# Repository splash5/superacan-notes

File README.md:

# superacan-notes

All research notes about super acan.

# About the controller

The official super acan controller is hard to find and not good for game playing.
But you can use the SNES controller on super acan with a custom adapter.
The controller protocol is the same as SNES, but the button mapping is a little different.

| Acan | SNES |
|------|------|
|A     |B     |
|B     |Y     |
|START |SELECT|
|SELECT|START |
|Up    |Up    |
|Down  |Down  |
|Left  |Left  |
|Right |Right |
|X     |A     |
|Y     |X     |
|L     |L     |
|R     |R     |

Not very sure and not tested but some game should support multitap (which never officially released, only mentioned on manual).

# About the 6650 chip

This acts as a CIC chip but only contains at least 32 bytes RAM and 16 bytes ROM. (No CPU inside it I guess)
When powering on the 68k CPU runs code which store inside 6619 chip (like Genesis TMSS) and doing some check
about 6650 (like make sure that RAM exists and work properly) and finally reads a special string and compare it.
CPU communicate to 6650 with two memory location(register):

- 0xEB0D03 (W)
> Which address to access inside 6650.
- 0xEB0D01 (R/W)
> Data on that address.

Booting procedure pseudo code:

    boolean booting_check(void) {
      const uint8_t special[] = {0x9b, 0x65, 0x70, 0x90, 0x29, 0x43, 0x28, 0x20, 0x34, 0x39, 0x39, 0x31, 0x20, 0x43, 0x4d, 0x55};
      const uint8_t *um6650_addr_reg = (uint8_t far *)0xeb0d03;
      const uint8_t *um6650_data_reg = (uint8_t far *)0xeb0d01;
      
      uint8_t count; 
      uint8_t mem[32];

      // backup values inside 6650
      for (count = 0; count < 32; count++) {
      	*um6650_addr_reg = 0x5f - count;
      	mem[count] = *um6650_data_reg;
      }
    
      // filling test pattern
      for (count = 0x5f; count <= 0x40; count--) {
        *um6650_addr_reg = count;
        *um6650_data_reg = count;
      }
    
      // check if previous writing succeed
      for (count = 0x5f; count <= 0x40; count--) {
        *um6650_addr_reg = count;
        
        if (*um6650_data_reg != count)
          return false;      
      }
      
      // restore values back to 6650
      for (count = 0; count < 32; count++) {
        *um6650_addr_reg = 0x5f - count;
        *um6650_data_reg = mem[count];
      }
      
      // check if special string matches
      for (count = 0; count < 16; count++) {
        *um6650_addr_reg = 0x2f - count;
        
        if (*um6650_data_reg != special[count])
          return false;      
      }
      
      // unknown purpose
      *um6650_addr_reg = 0x09;
      *um6650_data_reg = 0xff;
      
      *um6650_addr_reg = 0x0c;
      uint8_t tmp = *um6650_data_reg;	// tmp = 0xff
      *um6650_data_reg = 0x00;
            
      return true;
    }
Based on these info, I built a tiny PCB with a AT28C64B which stores the special string at 0x20 to 0x2f, and filled 0x40 to 0x5f with 0x40 to 0x5f accordingly. And It did pass the checking and the game boots up!

I put EAGLE schematic, board and gerber file in [here](pcb/eagle/UM6650C).If you want to build by yourself, you need to program AT28C64B with [this file](pcb/eagle/UM6650C/UM6650C.bin) first. After programming the AT28C64B, solder it on PCB and close the solder jumper next to C5 capacitor (mark with a tiny arrow). I also shared gerber on [oshpark](https://oshpark.com/shared_projects/0XdS5ExD) so you can order PCB from there.

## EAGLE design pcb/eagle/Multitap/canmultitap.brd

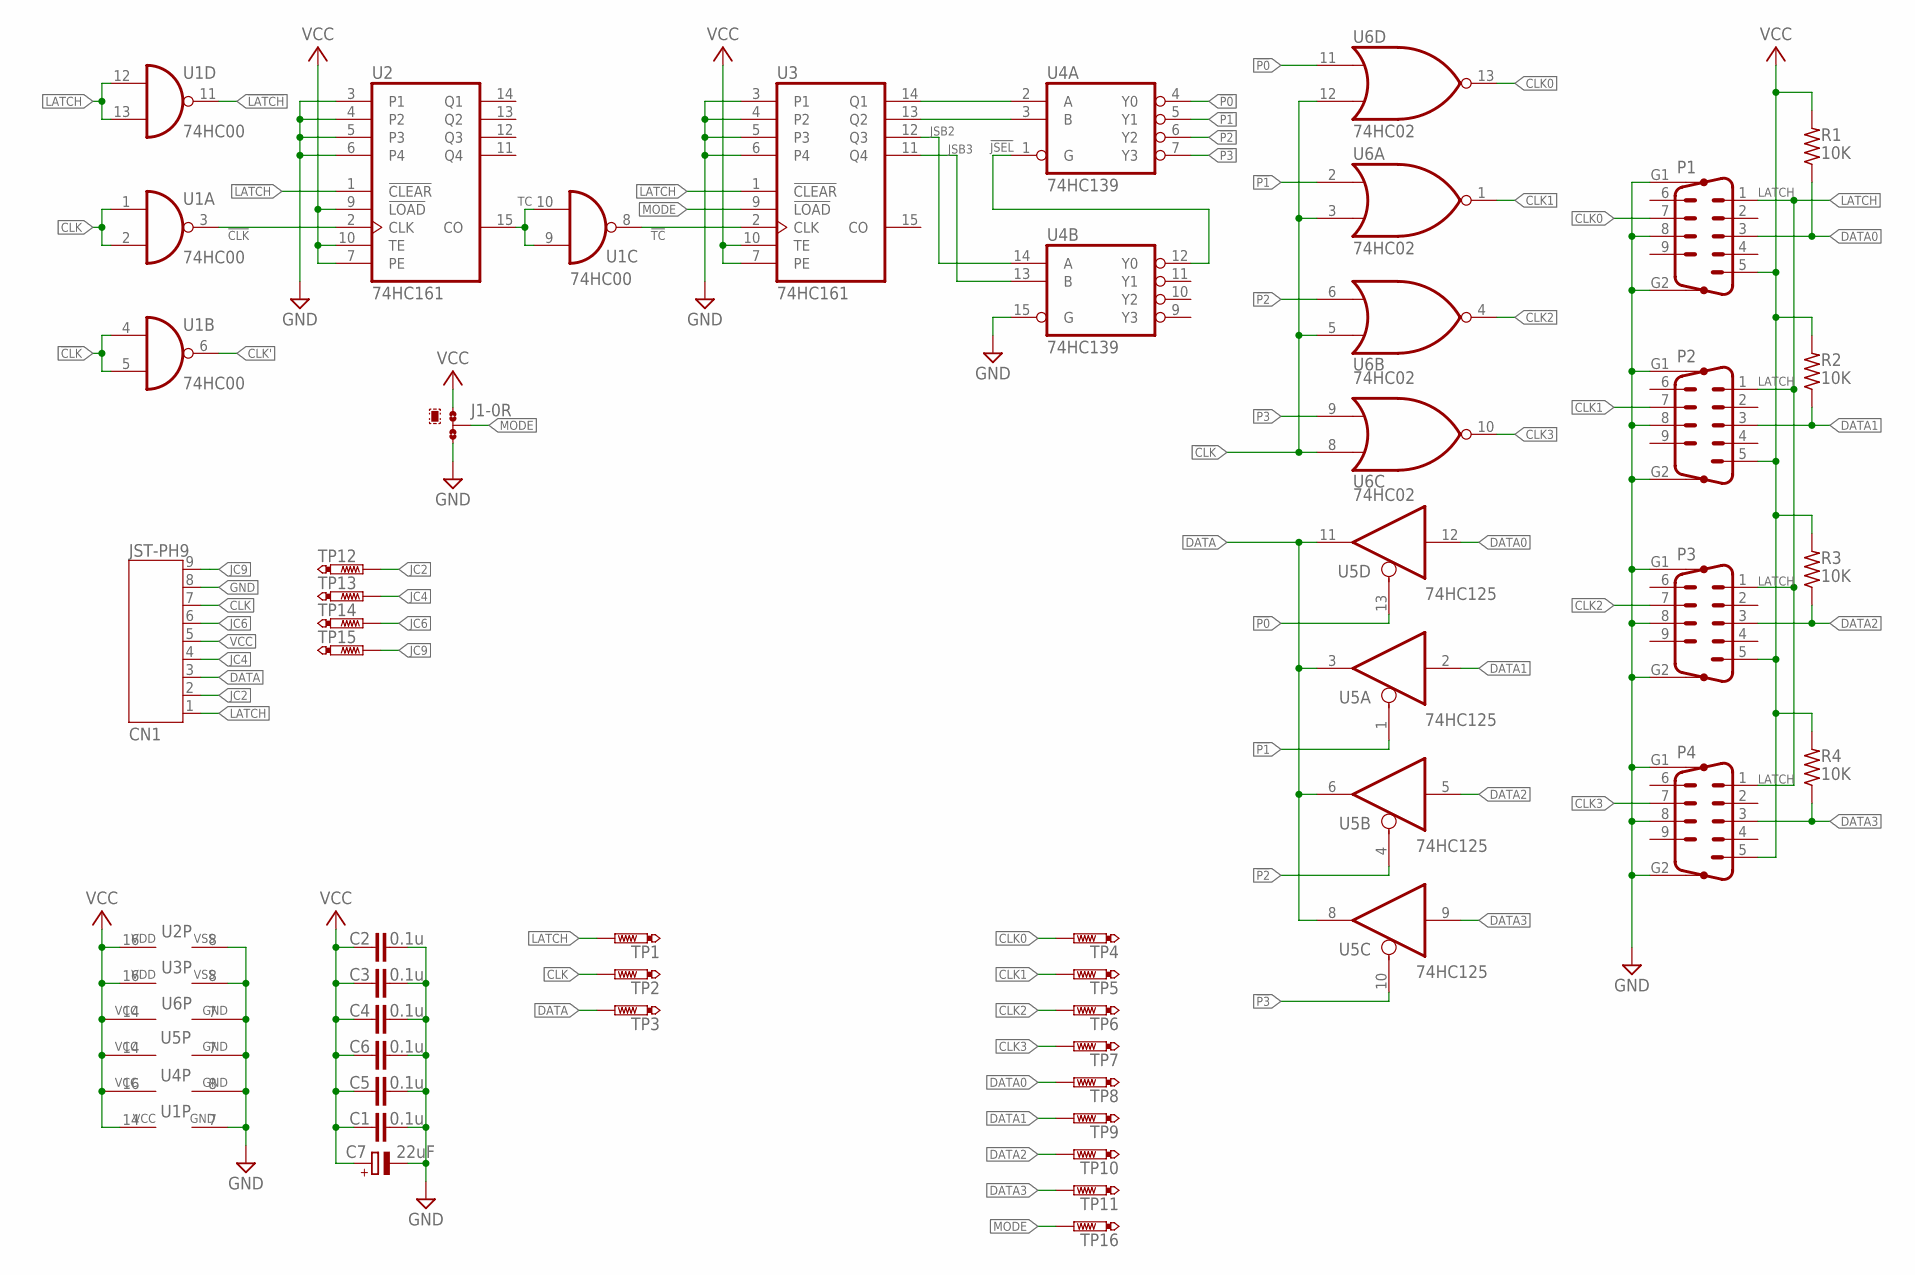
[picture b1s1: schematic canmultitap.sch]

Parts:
C1, C2, C3, C4, C5, C6: 0.1u; C0805
C7: 22uF; E2-4
CN1: JST-PH9
J1: 0R-JUMPA; A0R-JMP
P1, P2, P3, P4: M09HP
R1, R2, R3, R4: 10K; R0805
TP1, TP2, TP3, TP4, TP5, TP6, TP7, TP8, TP9, TP10, TP11, TP12, TP13, TP14, TP15, TP16: PTR1TP09R; TP09R
U1: 74HC00; TSSOP14
U2, U3: 74HC161; TSSOP16
U4: 74HC139; TSSOP16
U5: 74HC125; TSSOP14
U6: 74HC02; TSSOP14

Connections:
!CLK: U1.3 (O), U1.4 (I0), U1.5 (I1), U2.2 (CLK), U6.3 (I1), U6.5 (I0), U6.8 (I0), U6.12 (I1)
!JSEL: U4.1 (G), U4.12 (Y0)
!LATCH: U1.11 (O), U2.1 (!CLEAR), U3.1 (!CLEAR)
!P0: U4.4 (Y0), U5.13 (OE), U6.11 (I0)
!P1: U4.5 (Y1), U5.1 (OE), U6.2 (I0)
!P2: U4.6 (Y2), U5.4 (OE), U6.6 (I1)
!P3: U4.7 (Y3), U5.10 (OE), U6.9 (I1)
!TC: U1.8 (O), U3.2 (CLK)
CLK: CN1.7, TP2.TP, U1.1 (I0), U1.2 (I1)
CLK0: P1.7, TP4.TP, U6.13 (O)
CLK1: P2.7, TP5.TP, U6.1 (O)
CLK2: P3.7, TP6.TP, U6.4 (O)
CLK3: P4.7, TP7.TP, U6.10 (O)
CLK': U1.6 (O)
DATA: CN1.3, TP3.TP, U5.3 (O), U5.6 (O), U5.8 (O), U5.11 (O)
DATA0: P1.3, R1.1, TP8.TP, U5.12 (I)
DATA1: P2.3, R2.1, TP9.TP, U5.2 (I)
DATA2: P3.3, R3.1, TP10.TP, U5.5 (I)
DATA3: P4.3, R4.1, TP11.TP, U5.9 (I)
GND: C1.2, C2.2, C3.2, C4.2, C5.2, C6.2, C7.-, CN1.8, J1.3, P1.8, P1.G1, P1.G2, P2.8, P2.G1, P2.G2, P3.8, P3.G1, P3.G2, P4.8, P4.G1, P4.G2, U1.7 (GND), U2.3 (P1), U2.4 (P2), U2.5 (P3), U2.6 (P4), U2.8 (VSS), U3.3 (P1), U3.4 (P2), U3.5 (P3), U3.6 (P4), U3.8 (VSS), U4.8 (GND), U4.15 (G), U5.7 (GND), U6.7 (GND)
JC2: CN1.2, TP12.TP
JC4: CN1.4, TP13.TP
JC6: CN1.6, TP14.TP
JC9: CN1.9, TP15.TP
JSB0: U3.14 (Q1), U4.2 (A)
JSB1: U3.13 (Q2), U4.3 (B)
JSB2: U3.12 (Q3), U4.14 (A)
JSB3: U3.11 (Q4), U4.13 (B)
LATCH: CN1.1, P1.1, P2.1, P3.1, P4.1, TP1.TP, U1.12 (I0), U1.13 (I1)
MODE: J1.2, TP16.TP, U3.9 (!LOAD)
TC: U1.9 (I0), U1.10 (I1), U2.15 (CO)
VCC: C1.1, C2.1, C3.1, C4.1, C5.1, C6.1, C7.+, CN1.5, J1.1, P1.5, P2.5, P3.5, P4.5, R1.2, R2.2, R3.2, R4.2, U1.14 (VCC), U2.7 (PE), U2.9 (!LOAD), U2.10 (TE), U2.16 (VDD), U3.7 (PE), U3.10 (TE), U3.16 (VDD), U4.16 (VCC), U5.14 (VCC), U6.14 (VCC)

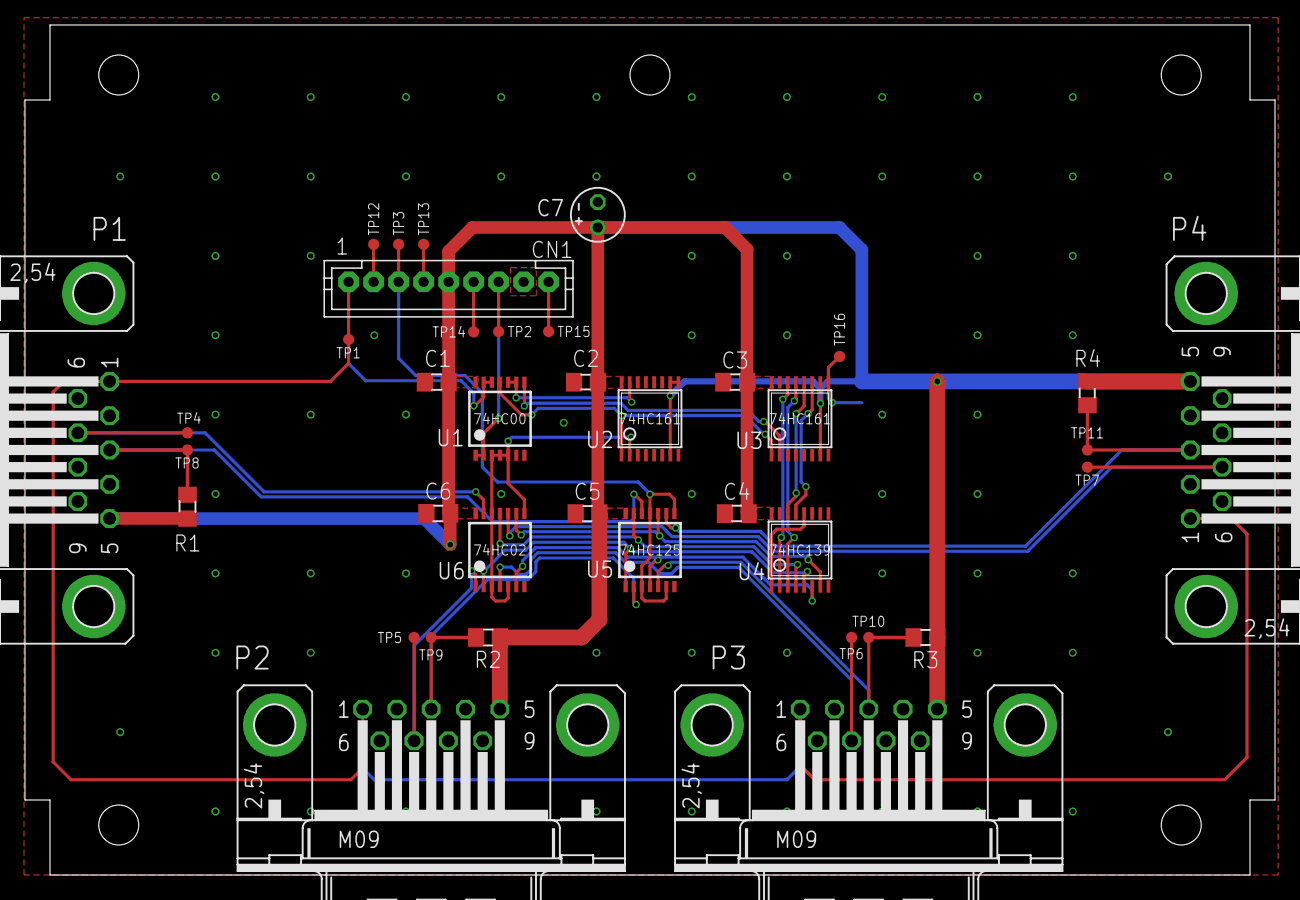
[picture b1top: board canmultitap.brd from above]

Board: 2 copper layers, 100.0 x 68.0 mm, 39 parts (1 on the bottom side), 31 nets.

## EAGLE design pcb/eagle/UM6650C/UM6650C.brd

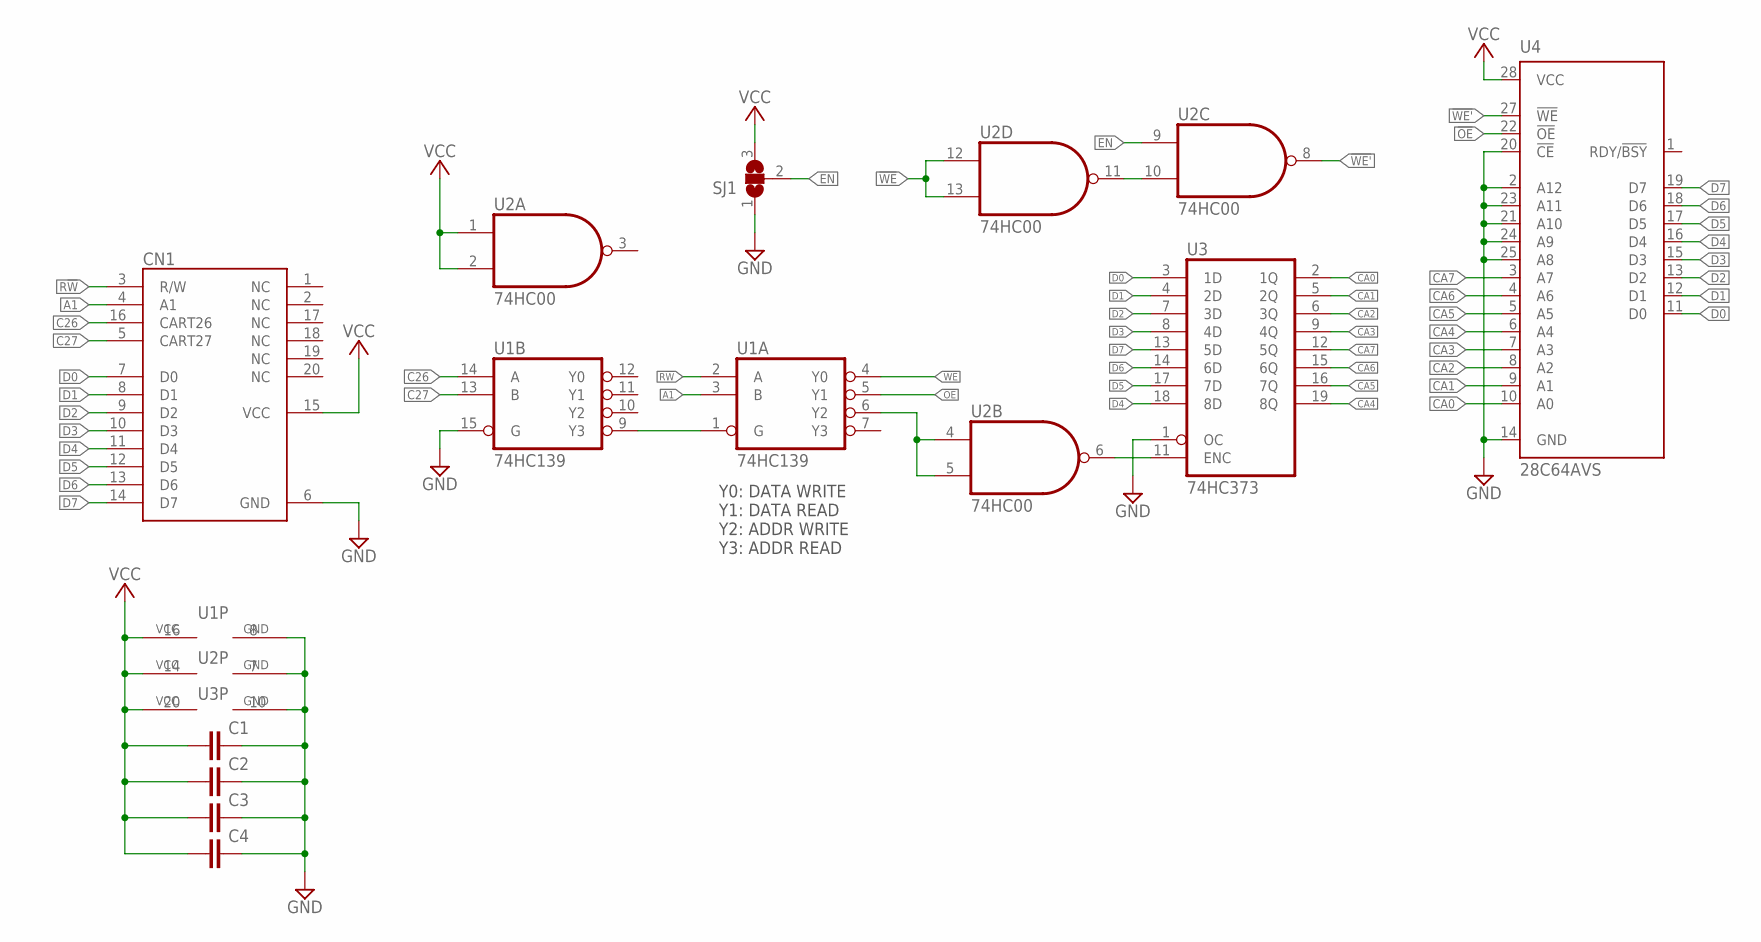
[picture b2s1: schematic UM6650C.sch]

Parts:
C1, C2, C3, C4: C-EUC0603; C0603
CN1: UM6650; DIL20
SJ1: SJ2W; SJ_2
U1: 74HC139; TSSOP16
U2: 74HC00; TSSOP14
U3: 74HC373; TSSOP20
U4: 28C64AVS; VSOP28-8X13

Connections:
!OE: U1.5 (Y1), U4.22 (!OE)
!WE: U1.4 (Y0), U2.12 (I0), U2.13 (I1)
!WE': U2.8 (O), U4.27 (!WE)
A1: CN1.4 (A1), U1.3 (B)
C26: CN1.16 (CART26), U1.14 (A)
C27: CN1.5 (CART27), U1.13 (B)
CA0: U3.2 (1Q), U4.10 (A0)
CA1: U3.5 (2Q), U4.9 (A1)
CA2: U3.6 (3Q), U4.8 (A2)
CA3: U3.9 (4Q), U4.7 (A3)
CA4: U3.19 (8Q), U4.6 (A4)
CA5: U3.16 (7Q), U4.5 (A5)
CA6: U3.15 (6Q), U4.4 (A6)
CA7: U3.12 (5Q), U4.3 (A7)
D0: CN1.7 (D0), U3.3 (1D), U4.11 (D0)
D1: CN1.8 (D1), U3.4 (2D), U4.12 (D1)
D2: CN1.9 (D2), U3.7 (3D), U4.13 (D2)
D3: CN1.10 (D3), U3.8 (4D), U4.15 (D3)
D4: CN1.11 (D4), U3.18 (8D), U4.16 (D4)
D5: CN1.12 (D5), U3.17 (7D), U4.17 (D5)
D6: CN1.13 (D6), U3.14 (6D), U4.18 (D6)
D7: CN1.14 (D7), U3.13 (5D), U4.19 (D7)
EN: SJ1.2, U2.9 (I0)
GND: C1.2, C2.2, C3.2, C4.2, CN1.6 (GND), SJ1.1, U1.8 (GND), U1.15 (G), U2.7 (GND), U3.1 (OC), U3.10 (GND), U4.2 (A12), U4.14 (GND), U4.20 (!CE), U4.21 (A10), U4.23 (A11), U4.24 (A9), U4.25 (A8)
unnamed: U2.10 (I1), U2.11 (O)
unnamed: U1.1 (G), U1.9 (Y3)
unnamed: U1.6 (Y2), U2.4 (I0), U2.5 (I1)
unnamed: U2.6 (O), U3.11 (ENC)
R!W: CN1.3 (R/W), U1.2 (A)
VCC: C1.1, C2.1, C3.1, C4.1, CN1.15 (VCC), SJ1.3, U1.16 (VCC), U2.1 (I0), U2.2 (I1), U2.14 (VCC), U3.20 (VCC), U4.28 (VCC)

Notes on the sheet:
Y0: DATA WRITE Y1: DATA READ Y2: ADDR WRITE Y3: ADDR READ

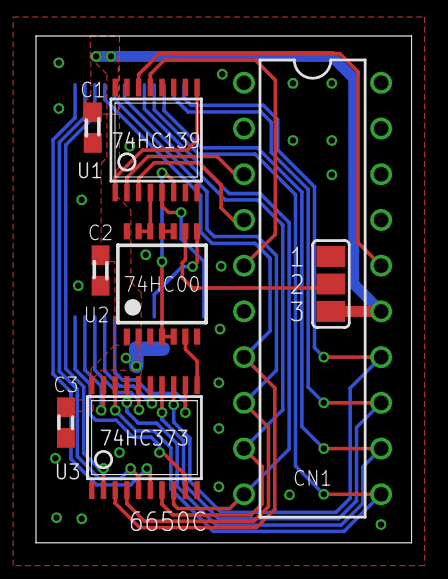
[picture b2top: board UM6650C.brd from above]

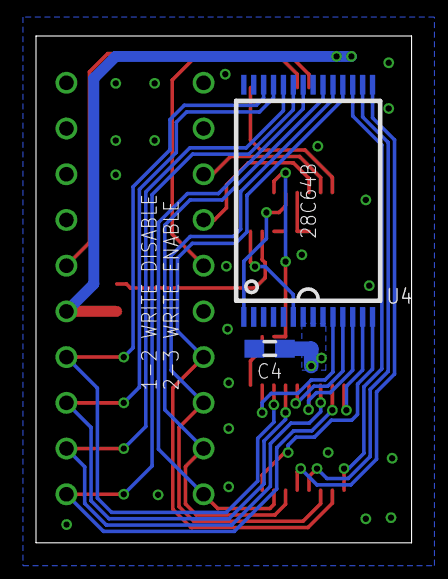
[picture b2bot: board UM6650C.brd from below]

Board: 2 copper layers, 20.9 x 28.2 mm, 10 parts (2 on the bottom side), 30 nets.

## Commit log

2020-04-22 Add EAGLE schematicss
2020-04-23 Add PCB photo scan
2020-04-24 Correct CPU BERR signal
    Add schematic's image file
2020-04-24 Correct CPU BERR signal
2020-04-29 Correct connections around Q1 and Q2.
2020-05-02 Add unlock procedure pseudo code
2020-05-02 Use pointer statement.
2020-05-03 Add comments
2021-01-07 Add 6650C related files
2021-01-07 Update README.md
    Update info about UM6650C
2021-07-31 Add Multitap schematic and board file
    Update UM6650C board file
2024-10-03 Correct Q3 related wiring
    (CV output)
2025-01-26 Correct 6650 address
2025-01-26 Update schematic image files
    Removed unused part in cartridge schematic
